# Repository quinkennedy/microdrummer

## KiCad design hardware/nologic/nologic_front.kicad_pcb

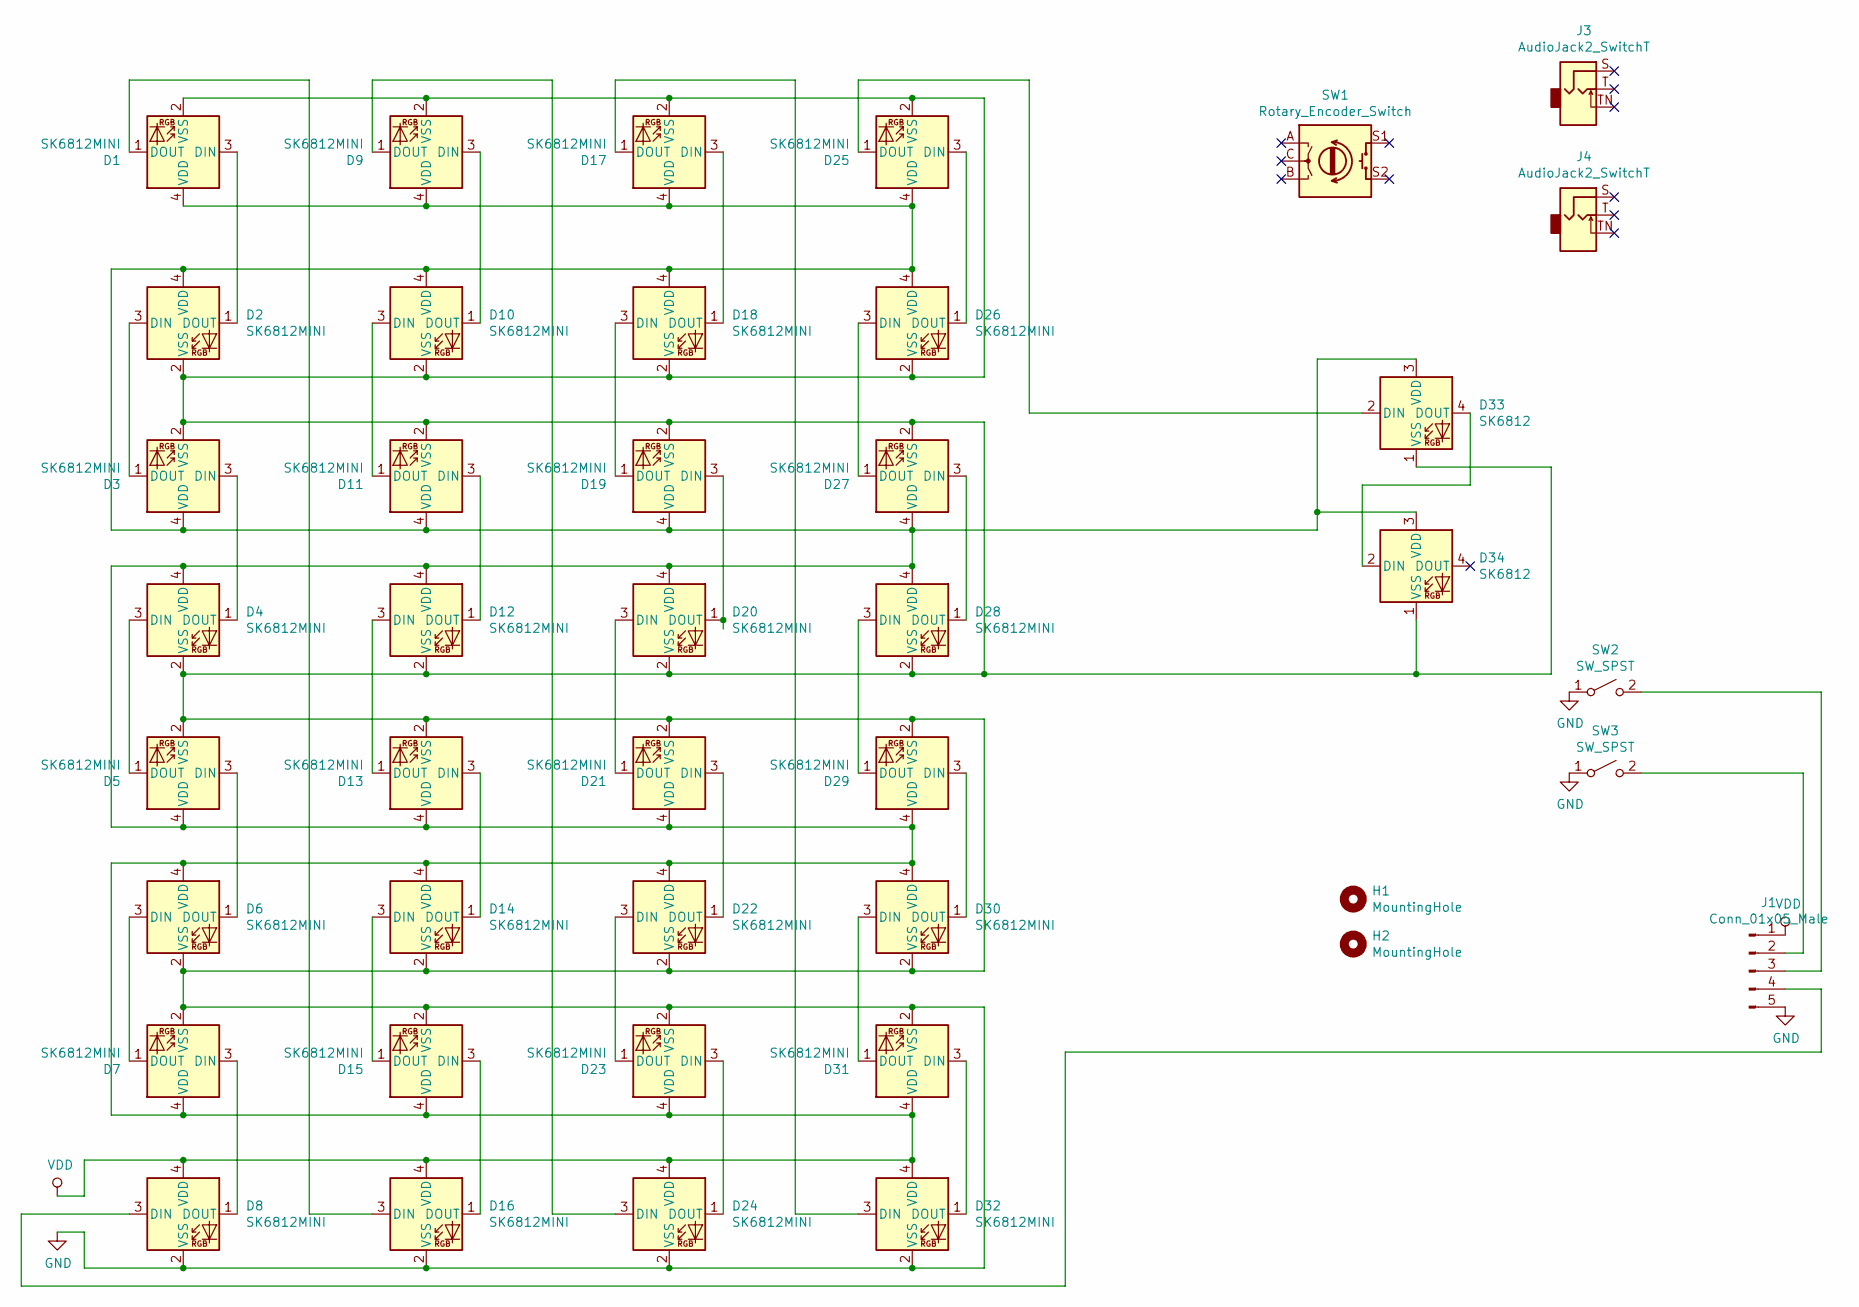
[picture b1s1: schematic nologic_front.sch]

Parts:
D1, D2, D3, D4, D5, D6, D7, D8, D9, D10, D11, D12, D13, D14, D15, D16, D17, D18, D19, D20, D21, D22, D23, D24, D25, D26, D27, D28, D29, D30, D31, D32: SK6812MINI; LED_SK6812MINI_PLCC4_3.5x3.5mm_P1.75mm_flush
D33, D34: SK6812; SK6812-MINI-E
H1, H2: MountingHole; M3_Slot
J1: Conn_01x05_Male; PinSocket_1x05_P2.54mm_Vertical_SMD_Pin1Left
J3, J4: AudioJack2_SwitchT; Jack_3.5mm_QingPu_WQP-PJ3410_Vertical_Top
SW1: Rotary_Encoder_Switch; Rotary_Encoder_Switched_PEC11R_top
SW2, SW3: SW_SPST; Kailh-PG1350-1u-NoLED

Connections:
GND: D1.2 (VSS), D2.2 (VSS), D3.2 (VSS), D4.2 (VSS), D5.2 (VSS), D6.2 (VSS), D7.2 (VSS), D8.2 (VSS), D9.2 (VSS), D10.2 (VSS), D11.2 (VSS), D12.2 (VSS), D13.2 (VSS), D14.2 (VSS), D15.2 (VSS), D16.2 (VSS), D17.2 (VSS), D18.2 (VSS), D19.2 (VSS), D20.2 (VSS), D21.2 (VSS), D22.2 (VSS), D23.2 (VSS), D24.2 (VSS), D25.2 (VSS), D26.2 (VSS), D27.2 (VSS), D28.2 (VSS), D29.2 (VSS), D30.2 (VSS), D31.2 (VSS), D32.2 (VSS), D33.1 (VSS), D34.1 (VSS), J1.5, SW2.1 (A), SW3.1 (A)
unnamed: D1.1 (DOUT), D16.3 (DIN)
unnamed: D1.3 (DIN), D2.1 (DOUT)
unnamed: D2.3 (DIN), D3.1 (DOUT)
unnamed: D3.3 (DIN), D4.1 (DOUT)
unnamed: D4.3 (DIN), D5.1 (DOUT)
unnamed: D5.3 (DIN), D6.1 (DOUT)
unnamed: D6.3 (DIN), D7.1 (DOUT)
unnamed: D7.3 (DIN), D8.1 (DOUT)
unnamed: D8.3 (DIN), J1.4
unnamed: D9.3 (DIN), D10.1 (DOUT)
unnamed: D10.3 (DIN), D11.1 (DOUT)
unnamed: D11.3 (DIN), D12.1 (DOUT)
unnamed: D12.3 (DIN), D13.1 (DOUT)
unnamed: D13.3 (DIN), D14.1 (DOUT)
unnamed: D14.3 (DIN), D15.1 (DOUT)
unnamed: D15.3 (DIN), D16.1 (DOUT)
unnamed: D17.1 (DOUT), D32.3 (DIN)
unnamed: D17.3 (DIN), D18.1 (DOUT)
unnamed: D18.3 (DIN), D19.1 (DOUT)
unnamed: D19.3 (DIN), D20.1 (DOUT)
unnamed: D20.3 (DIN), D21.1 (DOUT)
unnamed: D21.3 (DIN), D22.1 (DOUT)
unnamed: D22.3 (DIN), D23.1 (DOUT)
unnamed: D23.3 (DIN), D24.1 (DOUT)
unnamed: D9.1 (DOUT), D24.3 (DIN)
unnamed: D25.1 (DOUT), D33.2 (DIN)
unnamed: D25.3 (DIN), D26.1 (DOUT)
unnamed: D26.3 (DIN), D27.1 (DOUT)
unnamed: D27.3 (DIN), D28.1 (DOUT)
unnamed: D28.3 (DIN), D29.1 (DOUT)
unnamed: D29.3 (DIN), D30.1 (DOUT)
unnamed: D30.3 (DIN), D31.1 (DOUT)
unnamed: D31.3 (DIN), D32.1 (DOUT)
unnamed: D33.4 (DOUT), D34.2 (DIN)
unnamed: J1.2, SW3.2 (B)
unnamed: J1.3, SW2.2 (B)
VDD: D1.4 (VDD), D2.4 (VDD), D3.4 (VDD), D4.4 (VDD), D5.4 (VDD), D6.4 (VDD), D7.4 (VDD), D8.4 (VDD), D9.4 (VDD), D10.4 (VDD), D11.4 (VDD), D12.4 (VDD), D13.4 (VDD), D14.4 (VDD), D15.4 (VDD), D16.4 (VDD), D17.4 (VDD), D18.4 (VDD), D19.4 (VDD), D20.4 (VDD), D21.4 (VDD), D22.4 (VDD), D23.4 (VDD), D24.4 (VDD), D25.4 (VDD), D26.4 (VDD), D27.4 (VDD), D28.4 (VDD), D29.4 (VDD), D30.4 (VDD), D31.4 (VDD), D32.4 (VDD), D33.3 (VDD), D34.3 (VDD), J1.1

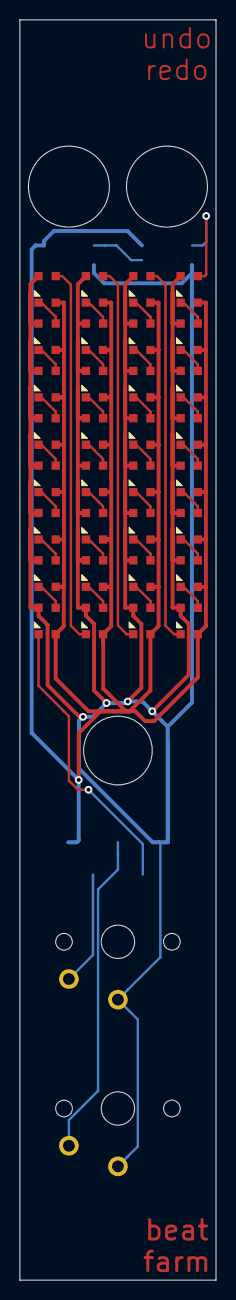
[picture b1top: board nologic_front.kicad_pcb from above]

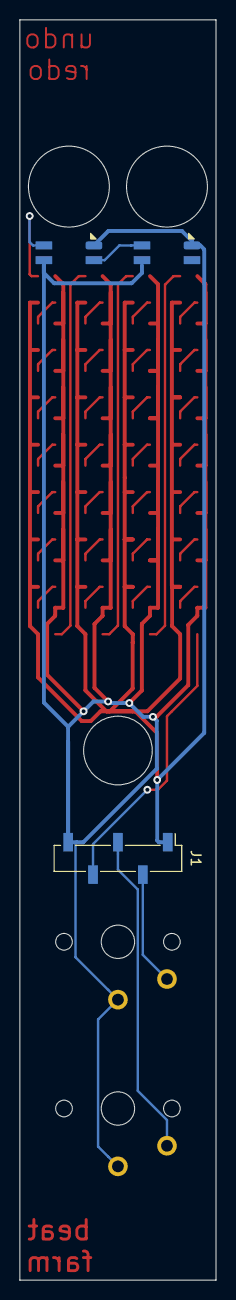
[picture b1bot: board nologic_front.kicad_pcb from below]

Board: 2 copper layers, 20.0 x 128.5 mm, 42 parts (3 on the bottom side), 38 nets.

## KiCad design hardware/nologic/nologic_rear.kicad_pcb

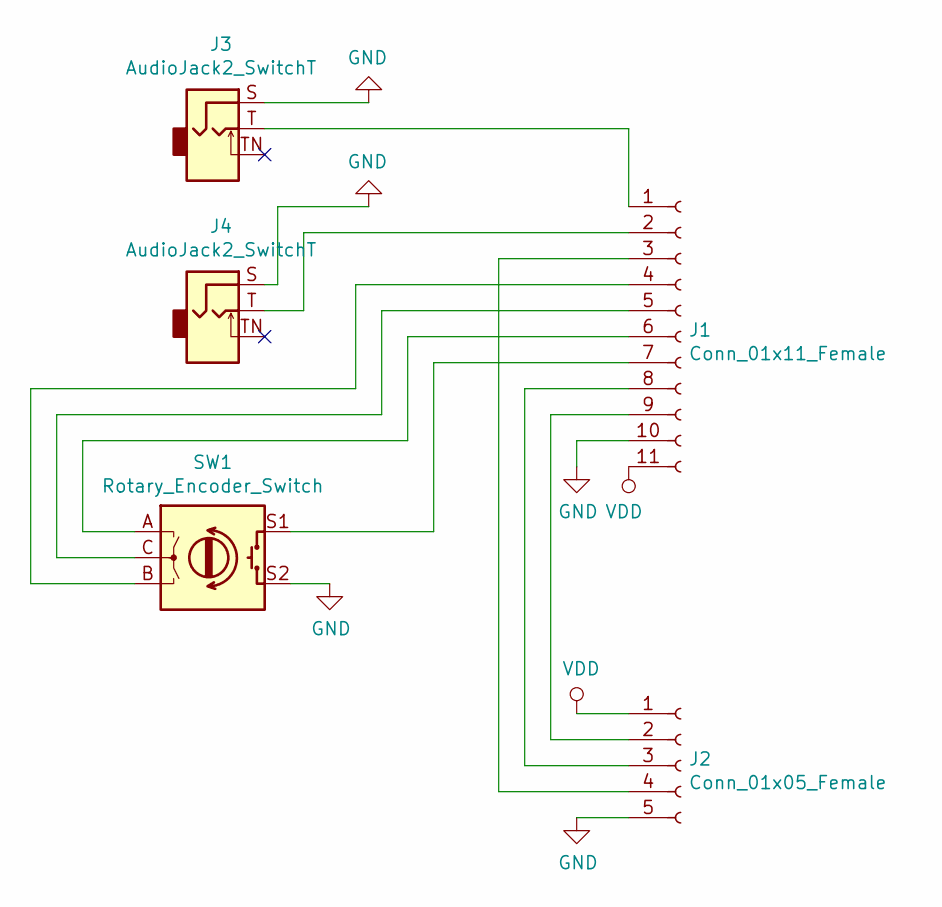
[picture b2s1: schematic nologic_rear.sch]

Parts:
J1: Conn_01x11_Female; PinSocket_1x11_P2.54mm_Horizontal
J2: Conn_01x05_Female; PinHeader_1x05_P2.54mm_Vertical
J3, J4: AudioJack2_SwitchT; Jack_3.5mm_QingPu_WQP-PJ3410_Vertical
SW1: Rotary_Encoder_Switch; Rotary_Encoder_Switched_PEC11R

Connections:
GND: J1.10, J2.5, J3.S, J4.S, SW1.S2
unnamed: J1.1, J3.T
unnamed: J1.2, J4.T
unnamed: J1.3, J2.4
unnamed: J1.4, SW1.B
unnamed: J1.5, SW1.C
unnamed: J1.6, SW1.A
unnamed: J1.7, SW1.S1
unnamed: J1.8, J2.3
unnamed: J1.9, J2.2
VDD: J1.11, J2.1

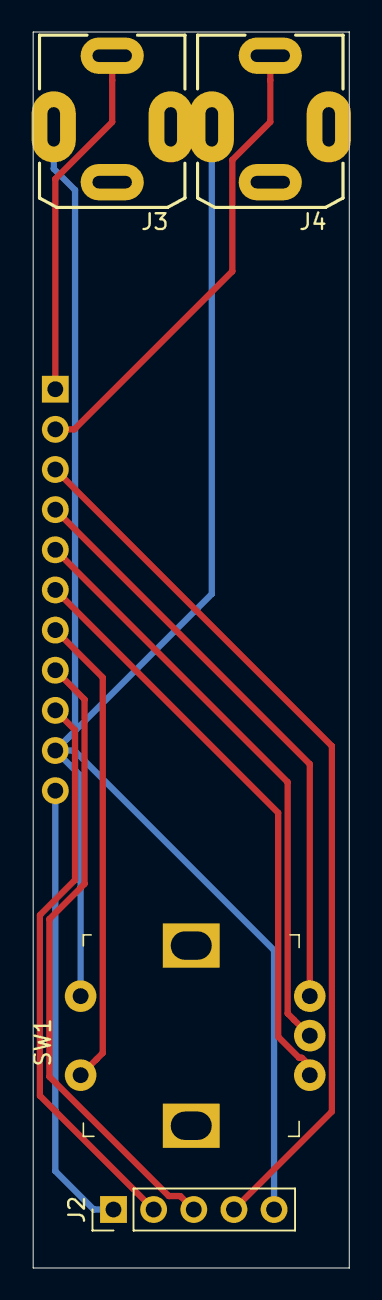
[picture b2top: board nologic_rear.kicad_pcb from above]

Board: 2 copper layers, 20.0 x 78.2 mm, 5 parts (1 on the bottom side), 11 nets.

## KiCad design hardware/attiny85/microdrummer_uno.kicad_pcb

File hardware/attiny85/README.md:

symbol libraries:

* http://www.sinphi.com/synths/miasma/miasma.html
  - thonk symbols
* https://github.com/benwis/SparkFun-Kicad-Libraries
  - little bits symbols
* https://github.com/nebs/eurocad
  - power connector
* https://github.com/keebio/keebio-components
  - key switch symbols

component libraries:

* https://github.com/keebio/Keebio-Parts.pretty
  - key switch footprints
* https://github.com/quinkennedy/chillpizza.pretty
  - specific component symbols
* https://github.com/Digi-Key/digikey-kicad-library
  - toggle switch footprint

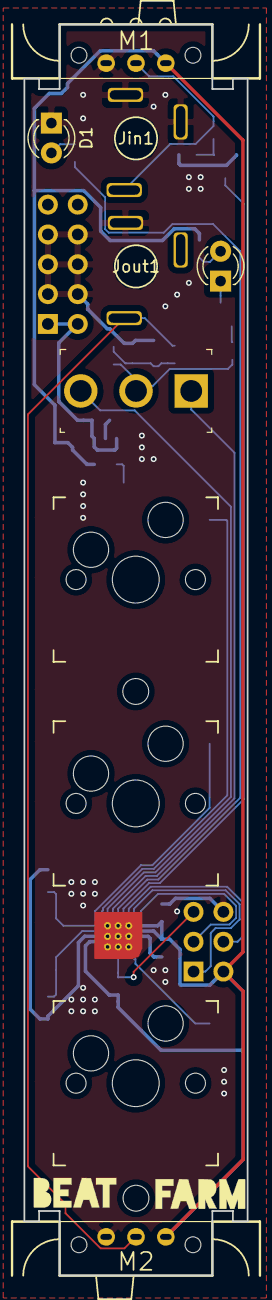
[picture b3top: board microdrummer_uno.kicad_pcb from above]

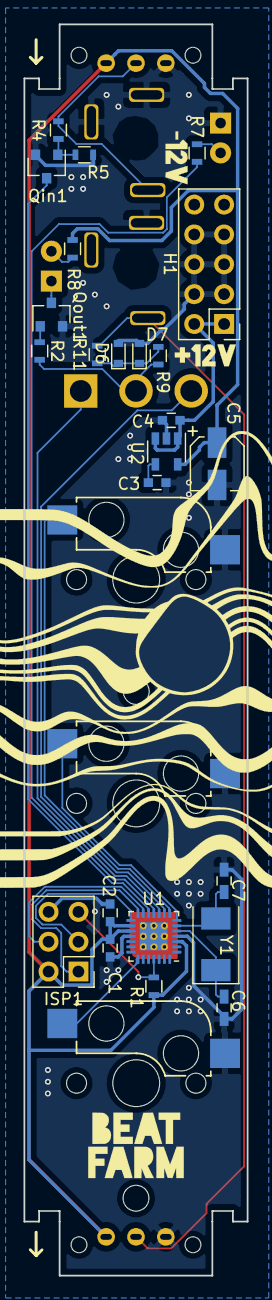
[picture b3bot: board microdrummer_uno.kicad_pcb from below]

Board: 2 copper layers, 19.0 x 106.5 mm, 34 parts (24 on the bottom side), 26 nets.

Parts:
C1: 10μF; C_0603
C2: 0.1μF; C_0603
C3: 470pF; C_0603
C4: 1μF; C_0603
C5: 2.2μF; CP_Elec_4x4.5
C6, C7: 30pF; C_0603_HandSoldering
D1: LED; LED_D3.0mm_FlatTop
D6: D_Zener; D_0603
D7: D_Schottky; D_0603
Dout1: LED; LED_D3.0mm_FlatTop
H1: EURO_PWR_2x5; PinHeader_2x05_P2.54mm_Vertical
ISP1: AVR-ISP-6; Pin_Header_Straight_2x03_Pitch2.54mm
Jin1: Thonk; schurter_3.5mm_mono_audio
Jout1: Thonk; schurter_3.5mm_mono_audio
M1: LITTLEBITS_MALE; LITTLE_BITS_MALE
M2: LITTLEBITS_FEMALE; LITTLE_BITS_FEMALE
Qin1: MMBT3904; SOT-23
Qout1: MMBT3904; SOT-23
R1: 10kΩ; R_0603
R2, R4: 100k; R_0603
R5: 1M; R_0603
R7, R8, R9, R11: 1k; R_0603
SELout1: SW_SPDT; Toggle_Switch_100SP1T1B4M2QE
U1: ATmega328-MMH; VQFN-28-1EP_4x4mm_P0.45mm_EP2.4x2.4mm_ThermalVias
U2: MIC5219-5.0YM5; SOT-23-5
Y1: 20MHz; Crystal_SMD_0603-2pin_6.0x3.5mm
bclr1: SW_SPST; Kailh_socket_MX
bin1: SW_SPST; Kailh_socket_MX_1.5v
brec1: SW_SPST; Kailh_socket_MX

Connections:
+5V: C1.2, C2.2, C5.1, ISP1.2, M1.V+, M2.V+, R1.1, R8.1, U1.3, U1.16, U1.17, U2.5
+12V: C4.1, H1.1, H1.2, U2.1, U2.3
/BTN_CLR: U1.8, bclr1.1
/BTN_IN: U1.22, bin1.1
/BTN_REC: U1.7, brec1.1
/IN_LED: R7.1, U1.11
/IN_SIGNAL: Qin1.3, U1.12
/ISP_MISO: ISP1.1, U1.14
/ISP_MOSI: ISP1.4, U1.13
/ISP_RST: ISP1.5, R1.2, U1.25
/ISP_SCK: ISP1.3, U1.15
/OUTPUT: M2.SIG, R11.1
/OUT_GATE: SELout1.1, U1.10
/OUT_TRIGGER: SELout1.3, U1.9
/RAW_OUTPUT: R2.1, R9.2, SELout1.2
/RAW_SIGNAL: M1.SIG, R4.2
GND: C1.1, C2.1, C3.2, C4.2, C5.2, C6.1, C7.1, D1.1, D6.2, D7.2, H1.3, H1.4, H1.5, H1.6, H1.7, H1.8, ISP1.6, M1.V-, M2.V-, Qin1.2, Qout1.2, R5.1, U1.4, U1.18, U1.29, U2.2, bclr1.2, bin1.2, brec1.2
unnamed: C3.1, U2.4
unnamed: C6.2, U1.5, Y1.1
unnamed: C7.2, U1.6, Y1.2
unnamed: D1.2, R7.2
unnamed: D6.1, D7.1, R9.1, R11.2
unnamed: Dout1.1, Qout1.3
unnamed: Dout1.2, R8.2
unnamed: Qin1.1, R4.1, R5.2
unnamed: Qout1.1, R2.2

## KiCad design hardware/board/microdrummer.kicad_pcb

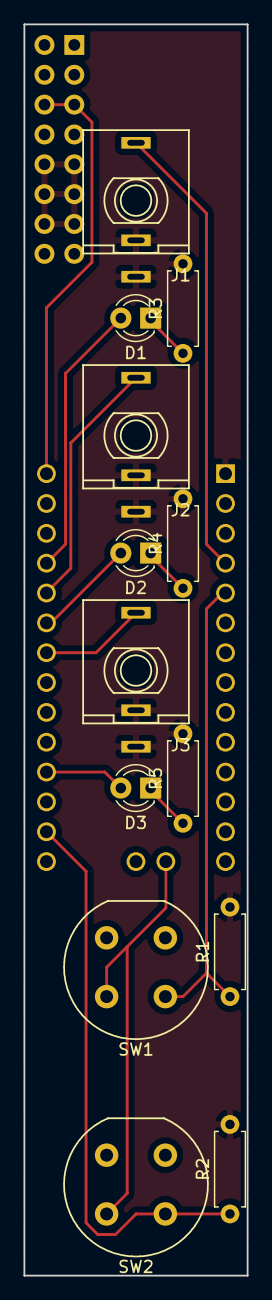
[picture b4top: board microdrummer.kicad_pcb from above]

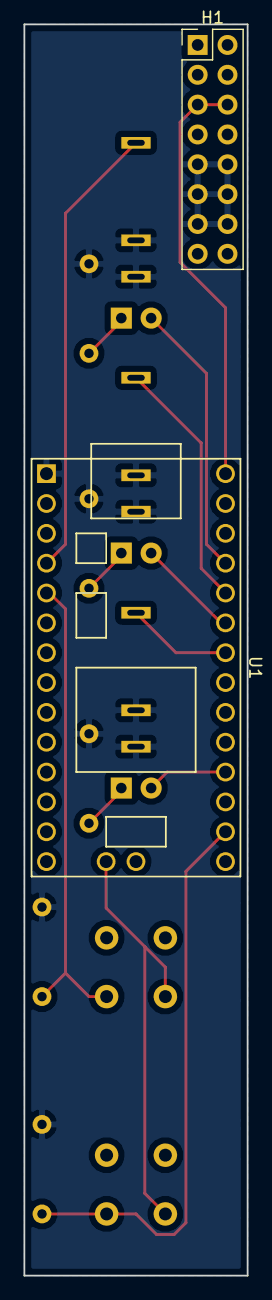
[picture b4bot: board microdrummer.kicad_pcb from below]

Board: 2 copper layers, 19.0 x 106.5 mm, 15 parts (2 on the bottom side), 14 nets.

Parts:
D1, D2, D3: LED; LED_D3.0mm_FlatTop
H1: EURO_PWR_2x8; Pin_Header_Straight_2x08_Pitch2.54mm
J1, J2, J3: Thonk; THONKICONN
R1, R2: 4.7k; R_Axial_DIN0207_L6.3mm_D2.5mm_P7.62mm_Horizontal
R3, R4, R5: 150; R_Axial_DIN0207_L6.3mm_D2.5mm_P7.62mm_Horizontal
SW1, SW2: SW_SPST; Push_E-Switch_KS01Q01
U1: Teensy3.2; Teensy30_31_32_LC_stdvgHeaders

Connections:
/BtnClr: R2.1, SW2.1, U1.21
/BtnIn: R1.1, SW1.1, U1.5
/GatLed: D2.2, U1.28
/GatOut: J2.3, U1.29
/SigIn: J1.3, U1.4
/SigLed: D1.2, U1.30
/TrgLed: D3.2, U1.23
/TrgOut: J3.3, U1.27
unnamed: D1.1, R3.1
unnamed: D2.1, R4.1
unnamed: D3.1, R5.1
unnamed: H1.5, H1.6, U1.33
unnamed: H1.9, H1.10, H1.11, H1.12, H1.13, H1.14, J1.1, J1.2, J2.1, J2.2, J3.1, J3.2, R1.2, R2.2, R3.2, R4.2, R5.2, U1.1
unnamed: SW1.2, SW2.2, U1.16

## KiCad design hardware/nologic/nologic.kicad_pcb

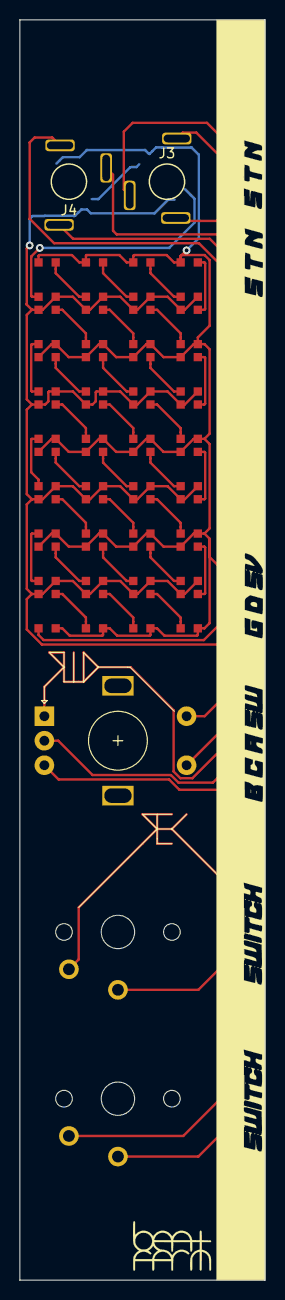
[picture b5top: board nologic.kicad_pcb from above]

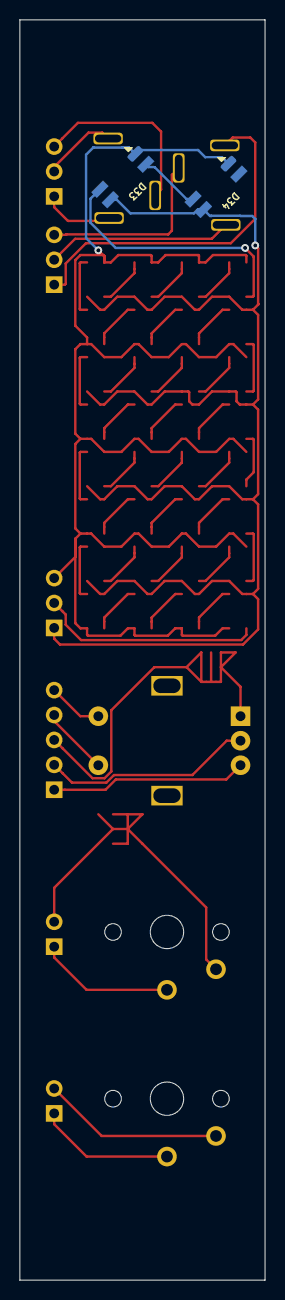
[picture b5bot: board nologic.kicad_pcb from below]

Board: 2 copper layers, 25.0 x 128.5 mm, 47 parts (2 on the bottom side), 51 nets.

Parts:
D1, D2, D3, D4, D5, D6, D7, D8, D9, D10, D11, D12, D13, D14, D15, D16, D17, D18, D19, D20, D21, D22, D23, D24, D25, D26, D27, D28, D29, D30, D31, D32: SK6812MINI; LED_SK6812MINI_PLCC4_3.5x3.5mm_P1.75mm
D33, D34: SK6812; SK6812-MINI-E
H1, H2: MountingHole; M3_Slot
J1, J5, J6: Conn_01x03_Female; PinHeader_1x03_P2.54mm_Vertical
J2: Conn_01x05_Female; PinHeader_1x05_P2.54mm_Vertical
J3, J4: AudioJack2_SwitchT; schurter_3.5mm_mono_audio_kicad
J7, J8: Conn_01x02_Female; PinHeader_1x02_P2.54mm_Vertical
SW1: Rotary_Encoder_Switch; RotaryEncoder_Alps_EC11E-Switch_Vertical_H20mm
SW2, SW3: SW_SPST; Kailh-PG1350-1u-NoLED

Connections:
unnamed: D1.1, D33.2
unnamed: D1.2, D2.2, D3.2, D4.2, D5.2, D6.2, D7.2, D8.2, D9.2, D10.2, D11.2, D12.2, D13.2, D14.2, D15.2, D16.2, D17.2, D18.2, D19.2, D20.2, D21.2, D22.2, D23.2, D24.2, D25.2, D26.2, D27.2, D28.2, D29.2, D30.2, D31.2, D32.2, D33.1, D34.1, J1.1
unnamed: D1.3, D9.1
unnamed: D1.4, D2.4, D3.4, D4.4, D5.4, D6.4, D7.4, D8.4, D9.4, D10.4, D11.4, D12.4, D13.4, D14.4, D15.4, D16.4, D17.4, D18.4, D19.4, D20.4, D21.4, D22.4, D23.4, D24.4, D25.4, D26.4, D27.4, D28.4, D29.4, D30.4, D31.4, D32.4, D33.3, D34.3, J1.3
unnamed: D2.3, D3.1
unnamed: D4.3, D5.1
unnamed: D6.3, D7.1
unnamed: D8.3, J1.2
unnamed: D10.1, D18.3
unnamed: D2.1, D10.3
unnamed: D3.3, D11.1
unnamed: D11.3, D19.1
unnamed: D12.1, D20.3
unnamed: D4.1, D12.3
unnamed: D5.3, D13.1
unnamed: D13.3, D21.1
unnamed: D14.1, D22.3
unnamed: D6.1, D14.3
unnamed: D7.3, D15.1
unnamed: D15.3, D23.1
unnamed: D16.1, D24.3
unnamed: D8.1, D16.3
unnamed: D9.3, D17.1
unnamed: D17.3, D25.1
unnamed: D18.1, D26.3
unnamed: D19.3, D27.1
unnamed: D20.1, D28.3
unnamed: D21.3, D29.1
unnamed: D22.1, D30.3
unnamed: D23.3, D31.1
unnamed: D24.1, D32.3
unnamed: D25.3, D26.1
unnamed: D27.3, D28.1
unnamed: D29.3, D30.1
unnamed: D31.3, D32.1
unnamed: D33.4, D34.2
unnamed: J2.1, SW1.B
unnamed: J2.2, SW1.C
unnamed: J2.3, SW1.A
unnamed: J2.4, SW1.S1
unnamed: J2.5, SW1.S2
unnamed: J3.S, J5.1
unnamed: J3.T, J5.2
unnamed: J3.TN, J5.3
unnamed: J4.S, J6.1
unnamed: J4.T, J6.2
unnamed: J4.TN, J6.3
unnamed: J7.1, SW2.1
unnamed: J7.2, SW2.2
unnamed: J8.1, SW3.1
unnamed: J8.2, SW3.2

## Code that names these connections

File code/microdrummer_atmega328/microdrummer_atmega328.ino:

#include <Bounce2.h>

//Inputs
#define IN_SIGNAL 10 
#define IN_LED 9
#define BTN_CLR 6
#define BTN_REC 5
#define BTN_IN 17
#define OUT_GATE 8
#define OUT_TRIGGER 7

Bounce sigB = Bounce();
Bounce recB = Bounce();
Bounce clrB = Bounce();
Bounce inB = Bounce();
//Other constants
const byte triggerDurationMs = 3;
const byte debounceDurationMs = 10;

struct Node {
  Node* next;
  uint16_t highTime;
  uint16_t lowTime;
};

//We will keep a singly-linked list of events
// so that we can efficiently insert events
Node* head = NULL;
Node* curr = NULL;
Node* prev = NULL;
uint16_t gateLowTime = 0;
uint16_t trigLowTime = 0;
unsigned long prevSignalRise = 0;
Node* holdingDown = NULL;
unsigned long heldDownAt = 0;
bool trigHigh = false;
bool gateHigh = false;
bool sigHigh = false;
bool tempGate = false;
uint16_t sinceRise = 0;

void setup(){
  //init inputs
  pinMode(IN_SIGNAL, INPUT_PULLUP);
  pinMode(BTN_IN, INPUT_PULLUP);
  pinMode(BTN_CLR, INPUT_PULLUP);
  pinMode(BTN_REC, INPUT_PULLUP);

  //init outputs
  pinMode(OUT_TRIGGER, OUTPUT);
  pinMode(OUT_GATE, OUTPUT);
  pinMode(IN_LED, OUTPUT);

  //set outputs low
  digitalWrite(OUT_TRIGGER, LOW);
  digitalWrite(OUT_GATE, LOW);
  digitalWrite(IN_LED, LOW);

  //init debouncing
  sigB.attach(IN_SIGNAL);
  sigB.interval(0);
  inB.attach(BTN_IN);
  inB.interval(debounceDurationMs);
  clrB.attach(BTN_CLR);
  clrB.interval(debounceDurationMs);
  recB.attach(BTN_REC);
  recB.interval(debounceDurationMs);
}

void loop(){
  
  //how far along are we in this sequence iteration
  sinceRise = (millis() - prevSignalRise);
  
  handleInputs();
  if (sigHigh && sinceRise > triggerDurationMs){
    sigHigh = false;
    digitalWrite(IN_LED, LOW);
  }

  //if the next event is scheduled to happen now
  if (curr != NULL && curr->highTime <= sinceRise){
    gateHigh = true;
    digitalWrite(OUT_GATE, HIGH);
    gateLowTime = max(gateLowTime, curr->lowTime);

    startTrigger();

    prev = curr;
    curr = curr->next;
  } else {
    if (gateHigh && holdingDown == NULL && sinceRise >= gateLowTime){
      gateHigh = false;
      if (!tempGate){
        digitalWrite(OUT_GATE, LOW);
      }
    }
    if (trigHigh && sinceRise >= trigLowTime){
      trigHigh = false;
      digitalWrite(OUT_TRIGGER, LOW);
    }
  }
}

inline void startTrigger(){
  if (!trigHigh){
    trigHigh = true;
    digitalWrite(OUT_TRIGGER, HIGH);
    trigLowTime = sinceRise + triggerDurationMs;
  }
}

inline void handleInputs(){
  recB.update();
  if (sigB.update()){
    if (sigB.fell()){
      restartSequence();
      sigHigh = true;
      digitalWrite(IN_LED, HIGH);
    }
  }
  if (inB.update()){
    if (inB.fell()){
      if (!recB.read()){
        insertEvent();
      } else {
        tempGate = true;
        digitalWrite(OUT_GATE, HIGH);
        startTrigger();
      }
    }
    else {
      finishEvent();
    }
  }
  if (!digitalRead(BTN_CLR)){
    clearEvents();
  }
}

//Start the sequence over
inline void restartSequence(){
  //wrap trigger and gate timers to new sequence
  uint16_t prevSequenceDuration = (millis() - prevSignalRise);

  if (gateLowTime <= prevSequenceDuration){
    gateLowTime = 0;
  } else {
    gateLowTime = gateLowTime - prevSequenceDuration;
  }
  
  if (trigLowTime <= prevSequenceDuration){
    trigLowTime = 0;
  } else {
    trigLowTime = trigLowTime - prevSequenceDuration;
  }
  
  //adjust timer for new sequence
  prevSignalRise = millis();
  sinceRise = 0;
  curr = head;
  prev = NULL;
}

//add an event to the sequence
inline void insertEvent(){
  //create the new event node
  Node* newest = new Node;
  newest->highTime = sinceRise;
  holdingDown = newest;
  heldDownAt = millis();

  //normally the next event has not triggered yet.
  // curr may be null if we have already reached the end of the sequence
  if (curr == NULL || sinceRise <= curr->highTime){
    newest->next = curr;
    curr = newest;
    if (prev == NULL){
      head = newest;
    } else {
      prev->next = newest;
    }
  } else {
    //there is a slight chance that the next event is delayed
    // because of loop timing. In this case we need to add the
    // new event after the next event.

    //theoretically it is possible that the new event should occur
    // after a number of simultaneous events,
    // so we need to walk the list
    Node* after = curr;
    while (after->next != NULL && after->next->highTime < sinceRise){
      after = after->next;
    }
    newest->next = after->next;
    after->next = newest;
  }
}

//Release the current gate
inline void finishEvent(){
  if (holdingDown != NULL){
    holdingDown->lowTime = ((millis() - heldDownAt) + holdingDown->highTime);
    //when you insert this event, it will set the gate low too early
    // in the case where there is another gate that spans this one
    gateLowTime = holdingDown->lowTime;
    holdingDown = NULL;
  } else if (tempGate){
    tempGate = false;
    if (!gateHigh){
      digitalWrite(OUT_GATE, LOW);
    }
  }
}

inline void clearEvents(){
  curr = head;
  //clear up the heap
  while(curr != NULL){
    prev = curr;
    curr = curr->next;
    delete prev;
  }
  //reset all variables
  head = NULL;
  prev = NULL;
  curr = NULL;
  holdingDown = NULL;
}

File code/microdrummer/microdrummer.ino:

//Inputs
const byte sigIn = 2;
const byte btnIn = 3;
const byte clrIn = 4;
//Outputs
const byte sigLed = 5;
const byte trigOutLed = 6;
const byte trigOut = 7;
const byte gateOutLed = 8;
const byte gateOut = 9;
//Other constants
const byte triggerDurationMs = 3;
const byte triggerLedDurationMs = 20;

struct Node {
  Node* next;
  uint16_t highTime;
  uint16_t lowTime;
};

//We will keep a singly-linked list of events
// so that we can efficiently insert events
Node* head = NULL;
Node* curr = NULL;
Node* prev = NULL;
uint16_t gateLowTime = 0;
uint16_t trigLowTime = 0;
uint16_t trigLedLowTime = 0;
unsigned long prevSignalRise = 0;
Node* holdingDown = NULL;
unsigned long heldDownAt = 0;
bool trigHigh = false;
bool trigLedHigh = false;
bool gateHigh = false;

void setup(){
  //init inputs
  pinMode(sigIn, INPUT);
  pinMode(btnIn, INPUT);
  pinMode(clrIn, INPUT);

  //init outputs
  pinMode(trigOutLed, OUTPUT);
  pinMode(trigOut, OUTPUT);
  pinMode(gateOutLed, OUTPUT);
  pinMode(gateOut, OUTPUT);

  //set outputs low
  digitalWrite(trigOutLed, LOW);
  digitalWrite(trigOut, LOW);
  digitalWrite(gateOutLed, LOW);
  digitalWrite(gateOut, LOW);

  //init interrupts
  attachInterrupt(digitalPinToInterrupt(sigIn), restartSequence, RISING);
  attachInterrupt(digitalPinToInterrupt(btnIn), insertEvent, RISING);
  attachInterrupt(digitalPinToInterrupt(btnIn), finishEvent, FALLING);
}

void loop(){
  //how far along are we in this sequence iteration
  uint16_t sinceRise = (millis() - prevSignalRise);

  //if the next event is scheduled to happen now
  if (curr != NULL && curr->highTime <= sinceRise){
    gateHigh = true;
    digitalWrite(gateOut, HIGH);
    digitalWrite(gateOutLed, HIGH);
    uint16_t currLowTime = curr->lowTime;
    gateLowTime = max(gateLowTime, curr->lowTime);
    
    trigHigh = true;
    digitalWrite(trigOut, HIGH);
    trigLowTime = sinceRise + triggerDurationMs;
    
    trigLedHigh = true;
    digitalWrite(trigOutLed, HIGH);
    trigLedLowTime = sinceRise + triggerLedDurationMs;
    
    curr = curr->next;
  } else {
    if (gateHigh && sinceRise >= gateLowTime){
      gateHigh = false;
      digitalWrite(gateOut, LOW);
      digitalWrite(gateOutLed, LOW);
    }
    if (trigHigh && sinceRise >= trigLowTime){
      trigHigh = false;
      digitalWrite(trigOut, LOW);
    }
    if (trigLedHigh && sinceRise >= trigLedLowTime){
      trigLedHigh = false;
      digitalWrite(trigOutLed, LOW);
    }
  }
}

//Start the sequence over
void restartSequence(){
  //wrap trigger and gate timers to new sequence
  uint16_t prevSequenceDuration = (millis() - prevSignalRise);

  if (gateLowTime <= prevSequenceDuration){
    gateLowTime = 0;
  } else {
    gateLowTime = gateLowTime - prevSequenceDuration;
  }
  
  if (trigLowTime <= prevSequenceDuration){
    trigLowTime = 0;
  } else {
    trigLowTime = trigLowTime - prevSequenceDuration;
  }

  if (trigLedLowTime <= prevSequenceDuration){
    trigLedLowTime = 0;
  } else {
    trigLedLowTime = trigLedLowTime = prevSequenceDuration;
  }
  
  //adjust timer for new sequence
  prevSignalRise = millis();
  curr = head;
  prev = NULL;
}

//add an event to the sequence
void insertEvent(){
  //how far along are we in this sequence iteration
  uint16_t sinceRise = (millis() - prevSignalRise);
  //create the new event node
  Node* newest = new Node;
  newest->highTime = sinceRise;
  holdingDown = newest;
  heldDownAt = millis();

  //normally the next event has not triggered yet.
  // curr may be null if we have already reached the end of the sequence
  if (curr == NULL || sinceRise <= curr->highTime){
    newest->next = curr;
    curr = newest;
    if (prev == NULL){
      head = newest;
    } else {
      prev->next = newest;
    }
  } else {
    //there is a slight chance that the next event is delayed
    // because of loop timing. In this case we need to add the
    // new event after the next event.

    //theoretically it is possible that the new event should occur
    // after a number of simultaneous events,
    // so we need to walk the list
    Node* after = curr;
    while (after->next != NULL && after->next->highTime < sinceRise){
      after = after->next;
    }
    newest->next = after->next;
    after->next = newest;
  }
}

//Release the current gate
void finishEvent(){
  if (holdingDown != NULL){
    holdingDown->lowTime = ((millis() - heldDownAt) + holdingDown->highTime);
    holdingDown = NULL;
  }
}

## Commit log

2018-07-01 start of a eurorack module
2018-07-01 Untested first pass at code.
2018-07-01 added some inputs and outputs, no new logic though.
2018-07-03 starting PCB layout
2018-07-03 Laid out PCB
    I had to move some of the pins around.
    I still need to update the code to match.
2018-07-04 created layout of front panel
2018-07-09 layout updates, and moved pins around for 1-layer routing
2020-11-09 fixed early close of new gates
    gates stay high as long as button is pressed
    migrated to atmega328 chip (_uno kicad files)
2020-11-09 added record button functionality
2021-02-02 including schematic cache
2021-02-02 documenting kicad libraries
2021-02-02 rescued symbols and migrated to kicad symbols
2021-05-24 code for prototype on qtpi
2021-05-24 new events replace undos
2021-05-24 lengthened trigger duration to make LED more visible
2021-05-26 using neopixel wing
2021-05-28 PC-based LED visualization
2021-11-19 v0.3 nologic prototype
2021-11-19 code updates for nologic
2021-11-20 starting rear panel
2021-11-22 front and rear graphics
